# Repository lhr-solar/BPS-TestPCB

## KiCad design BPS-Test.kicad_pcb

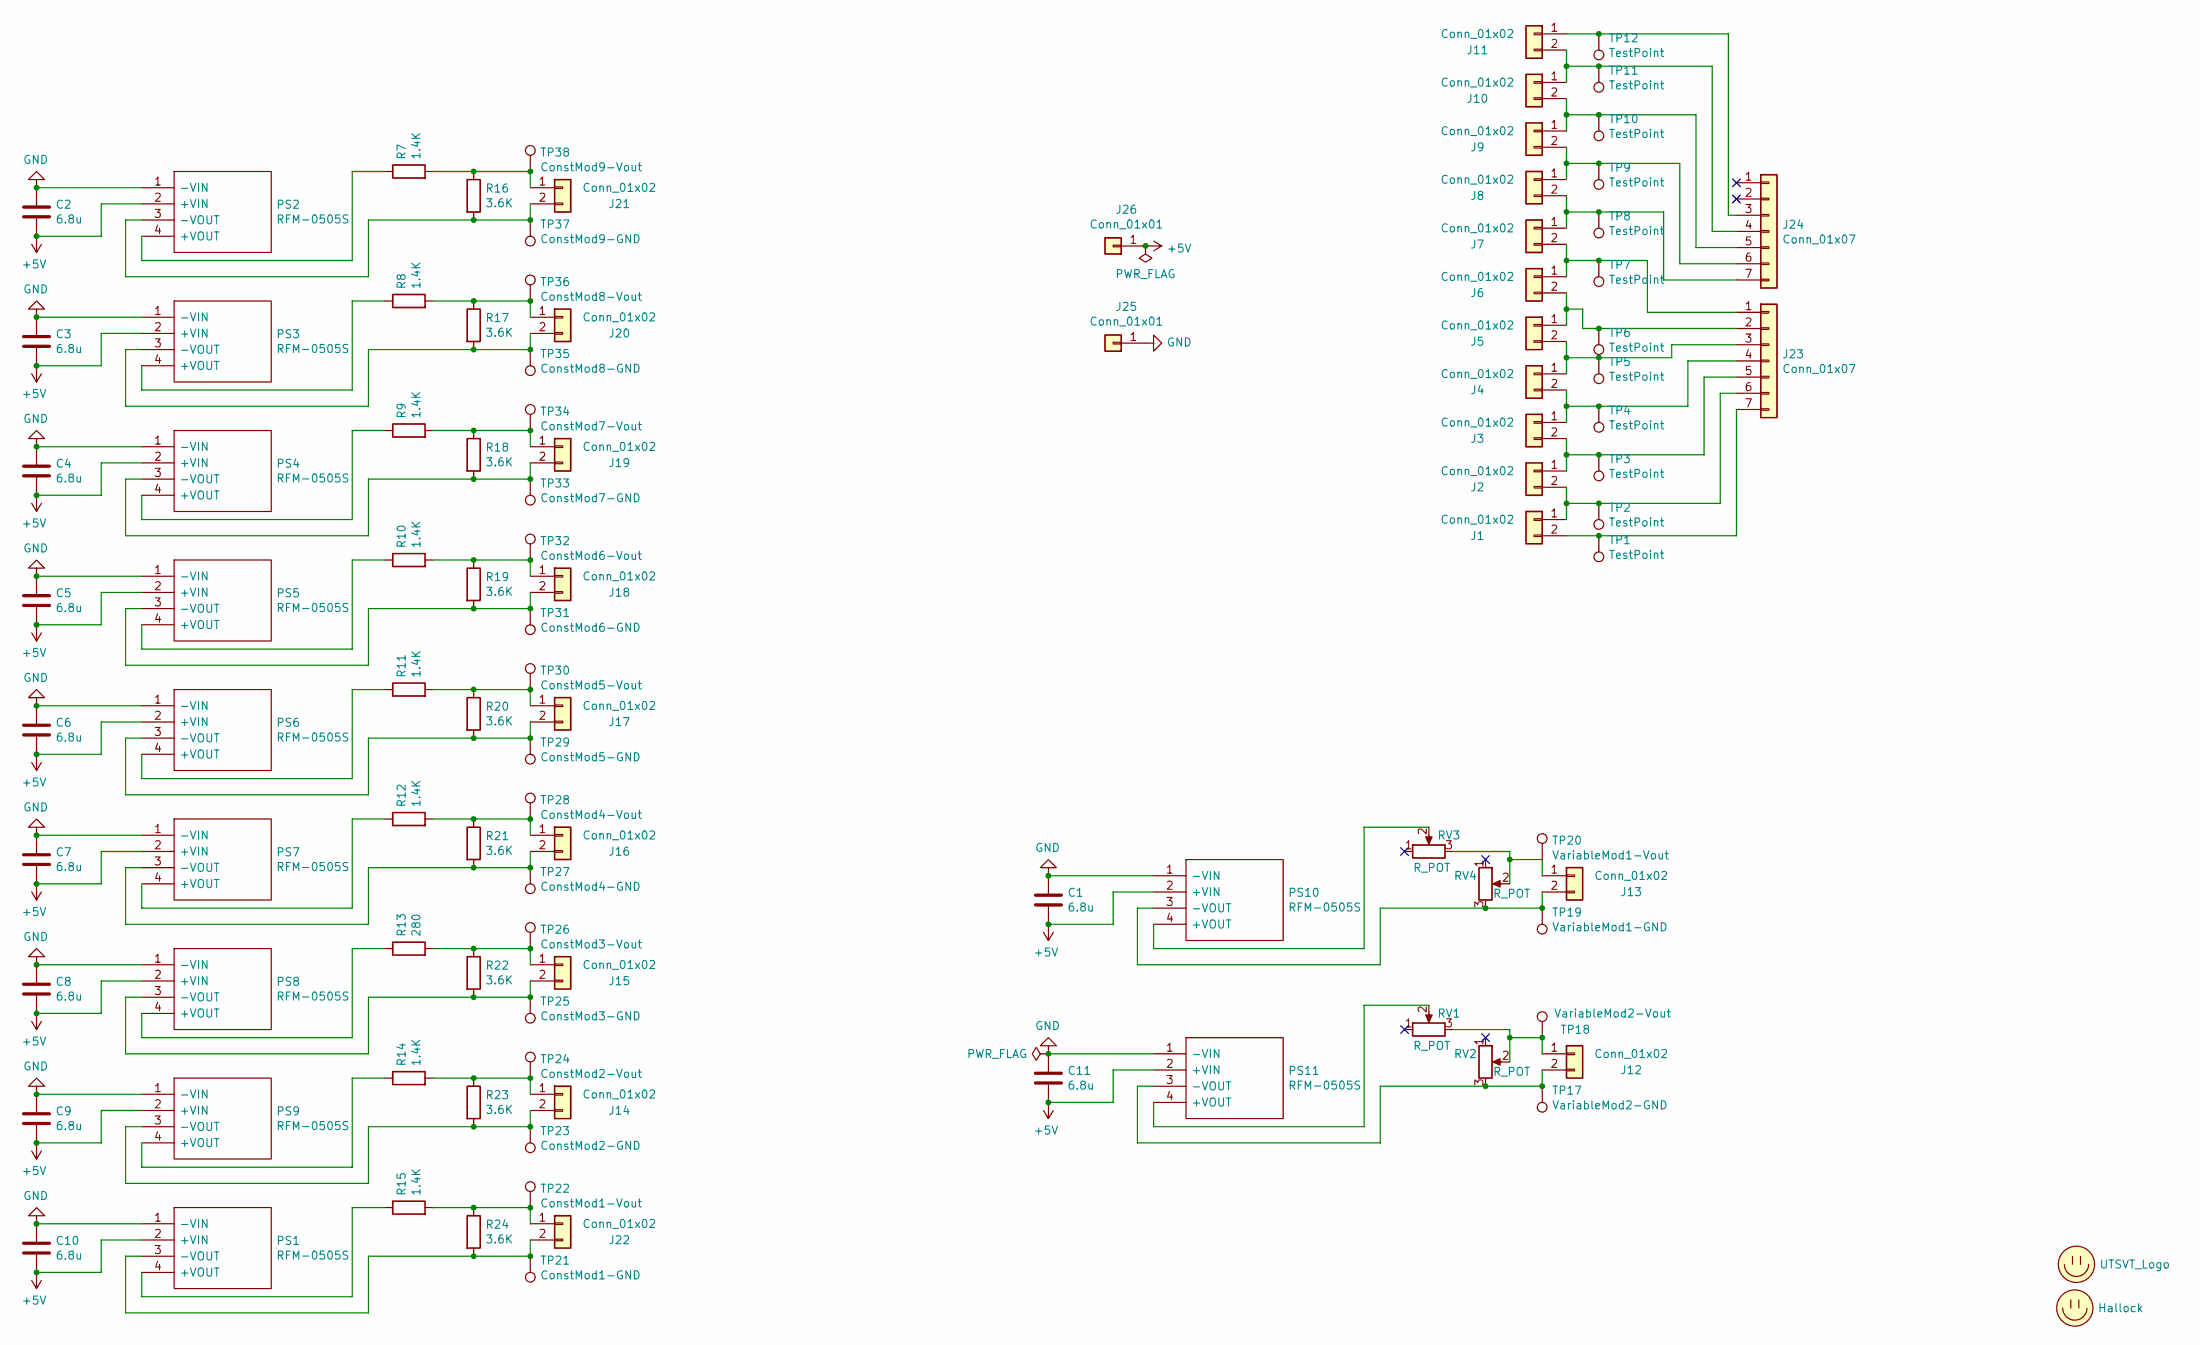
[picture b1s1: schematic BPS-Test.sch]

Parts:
C1, C2, C3, C4, C5, C6, C7, C8, C9, C10, C11: 6.8u; C_0805_2012Metric
J1, J2, J3, J4, J5, J6, J7, J8, J9, J10, J11, J12, J13, J14, J15, J16, J17, J18, J19, J20, J21, J22: Conn_01x02; PinHeader_1x02_P2.54mm_Vertical
J23, J24: Conn_01x07; Molex_MicroFit_01x07_Horizontal
J25, J26: Conn_01x01; Banana_Jack_1_Pin_4mm
LOGO1: Hallock; Hallock_Image
LOGO2: UTSVT_Logo; UTSVT_Logo_Symbol
PS1, PS2, PS3, PS4, PS5, PS6, PS7, PS8, PS9, PS10, PS11: RFM-0505S; RFM0505S; Mouser Part Number 919-RFM-0505S
R7, R8, R9, R10, R11, R12, R14, R15: 1.4K; R_0805_2012Metric
R13: 280; R_0805_2012Metric
R16, R17, R18, R19, R20, R21, R22, R23, R24: 3.6K; R_0805_2012Metric
RV1, RV2, RV3, RV4: R_POT; Potentiometer_Piher_PT-6-V_Vertical_Hole
TP1, TP2, TP3, TP4, TP5, TP6, TP7, TP8, TP9, TP10, TP11, TP12: TestPoint; TestPoint_Pad_2.0x2.0mm
TP17: VariableMod2-GND; TestPoint_Pad_2.0x2.0mm
TP18: VariableMod2-Vout; TestPoint_Pad_2.0x2.0mm
TP19: VariableMod1-GND; TestPoint_Pad_2.0x2.0mm
TP20: VariableMod1-Vout; TestPoint_Pad_2.0x2.0mm
TP21: ConstMod1-GND; TestPoint_Pad_2.0x2.0mm
TP22: ConstMod1-Vout; TestPoint_Pad_2.0x2.0mm
TP23: ConstMod2-GND; TestPoint_Pad_2.0x2.0mm
TP24: ConstMod2-Vout; TestPoint_Pad_2.0x2.0mm
TP25: ConstMod3-GND; TestPoint_Pad_2.0x2.0mm
TP26: ConstMod3-Vout; TestPoint_Pad_2.0x2.0mm
TP27: ConstMod4-GND; TestPoint_Pad_2.0x2.0mm
TP28: ConstMod4-Vout; TestPoint_Pad_2.0x2.0mm
TP29: ConstMod5-GND; TestPoint_Pad_2.0x2.0mm
TP30: ConstMod5-Vout; TestPoint_Pad_2.0x2.0mm
TP31: ConstMod6-GND; TestPoint_Pad_2.0x2.0mm
TP32: ConstMod6-Vout; TestPoint_Pad_2.0x2.0mm
TP33: ConstMod7-GND; TestPoint_Pad_2.0x2.0mm
TP34: ConstMod7-Vout; TestPoint_Pad_2.0x2.0mm
TP35: ConstMod8-GND; TestPoint_Pad_2.0x2.0mm
TP36: ConstMod8-Vout; TestPoint_Pad_2.0x2.0mm
TP37: ConstMod9-GND; TestPoint_Pad_2.0x2.0mm
TP38: ConstMod9-Vout; TestPoint_Pad_2.0x2.0mm

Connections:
+5V: C1.2, C2.2, C3.2, C4.2, C5.2, C6.2, C7.2, C8.2, C9.2, C10.2, C11.2, J26.1, PS1.2 (+VIN), PS2.2 (+VIN), PS3.2 (+VIN), PS4.2 (+VIN), PS5.2 (+VIN), PS6.2 (+VIN), PS7.2 (+VIN), PS8.2 (+VIN), PS9.2 (+VIN), PS10.2 (+VIN), PS11.2 (+VIN)
GND: C1.1, C2.1, C3.1, C4.1, C5.1, C6.1, C7.1, C8.1, C9.1, C10.1, C11.1, J25.1, PS1.1 (-VIN), PS2.1 (-VIN), PS3.1 (-VIN), PS4.1 (-VIN), PS5.1 (-VIN), PS6.1 (-VIN), PS7.1 (-VIN), PS8.1 (-VIN), PS9.1 (-VIN), PS10.1 (-VIN), PS11.1 (-VIN)
unnamed: J1.1, J2.2, J23.6, TP2.1
unnamed: J1.2, J23.7, TP1.1
unnamed: J2.1, J3.2, J23.5, TP3.1
unnamed: J10.1, J11.2, J24.4, TP11.1
unnamed: J9.1, J10.2, J24.5, TP10.1
unnamed: J11.1, J24.3, TP12.1
unnamed: J12.1, RV1.3, RV2.2, TP18.1
unnamed: J12.2, PS11.3 (-VOUT), RV2.3, TP17.1
unnamed: J13.1, RV3.3, RV4.2, TP20.1
unnamed: J13.2, PS10.3 (-VOUT), RV4.3, TP19.1
unnamed: J14.1, R14.2, R23.1, TP24.1
unnamed: J14.2, PS9.3 (-VOUT), R23.2, TP23.1
unnamed: J15.1, R13.2, R22.1, TP26.1
unnamed: J15.2, PS8.3 (-VOUT), R22.2, TP25.1
unnamed: J16.1, R12.2, R21.1, TP28.1
unnamed: J16.2, PS7.3 (-VOUT), R21.2, TP27.1
unnamed: J17.1, R11.2, R20.1, TP30.1
unnamed: J17.2, PS6.3 (-VOUT), R20.2, TP29.1
unnamed: J18.1, R10.2, R19.1, TP32.1
unnamed: J18.2, PS5.3 (-VOUT), R19.2, TP31.1
unnamed: J19.1, R9.2, R18.1, TP34.1
unnamed: J19.2, PS4.3 (-VOUT), R18.2, TP33.1
unnamed: J20.1, R8.2, R17.1, TP36.1
unnamed: J20.2, PS3.3 (-VOUT), R17.2, TP35.1
unnamed: J21.1, R7.2, R16.1, TP38.1
unnamed: J21.2, PS2.3 (-VOUT), R16.2, TP37.1
unnamed: J22.1, R15.2, R24.1, TP22.1
unnamed: J22.2, PS1.3 (-VOUT), R24.2, TP21.1
unnamed: J6.1, J7.2, J23.1, TP7.1
unnamed: J5.1, J6.2, J23.2, TP6.1
unnamed: J4.1, J5.2, J23.3, TP5.1
unnamed: J3.1, J4.2, J23.4, TP4.1
unnamed: J8.1, J9.2, J24.6, TP9.1
unnamed: J7.1, J8.2, J24.7, TP8.1
unnamed: PS1.4 (+VOUT), R15.1
unnamed: PS2.4 (+VOUT), R7.1
unnamed: PS3.4 (+VOUT), R8.1
unnamed: PS4.4 (+VOUT), R9.1
unnamed: PS5.4 (+VOUT), R10.1
unnamed: PS6.4 (+VOUT), R11.1
unnamed: PS7.4 (+VOUT), R12.1
unnamed: PS8.4 (+VOUT), R13.1
unnamed: PS9.4 (+VOUT), R14.1
unnamed: PS10.4 (+VOUT), RV3.2
unnamed: PS11.4 (+VOUT), RV1.2

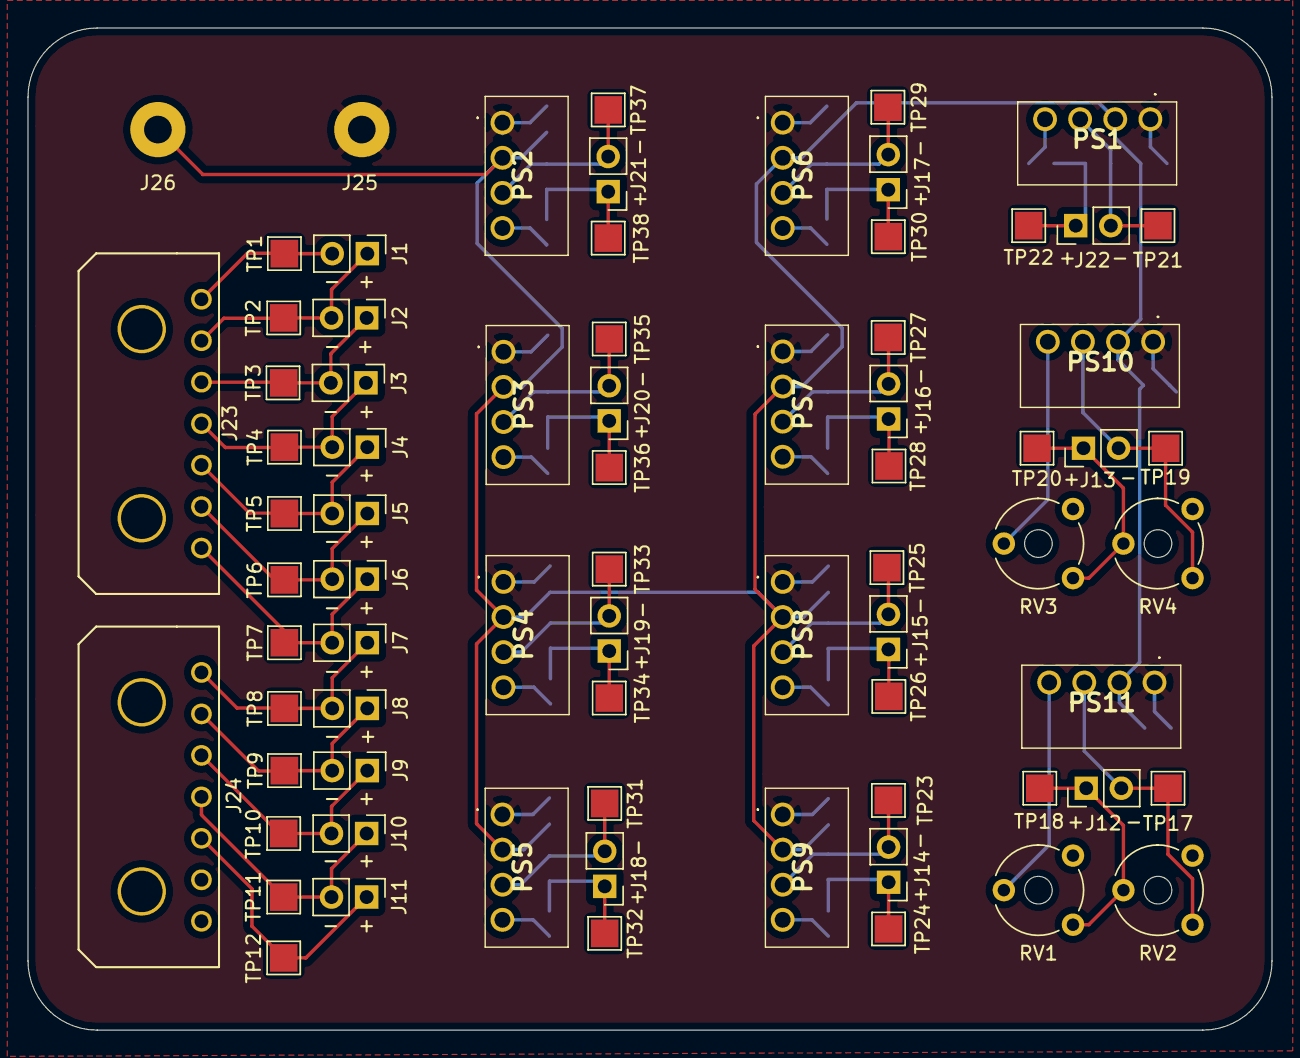
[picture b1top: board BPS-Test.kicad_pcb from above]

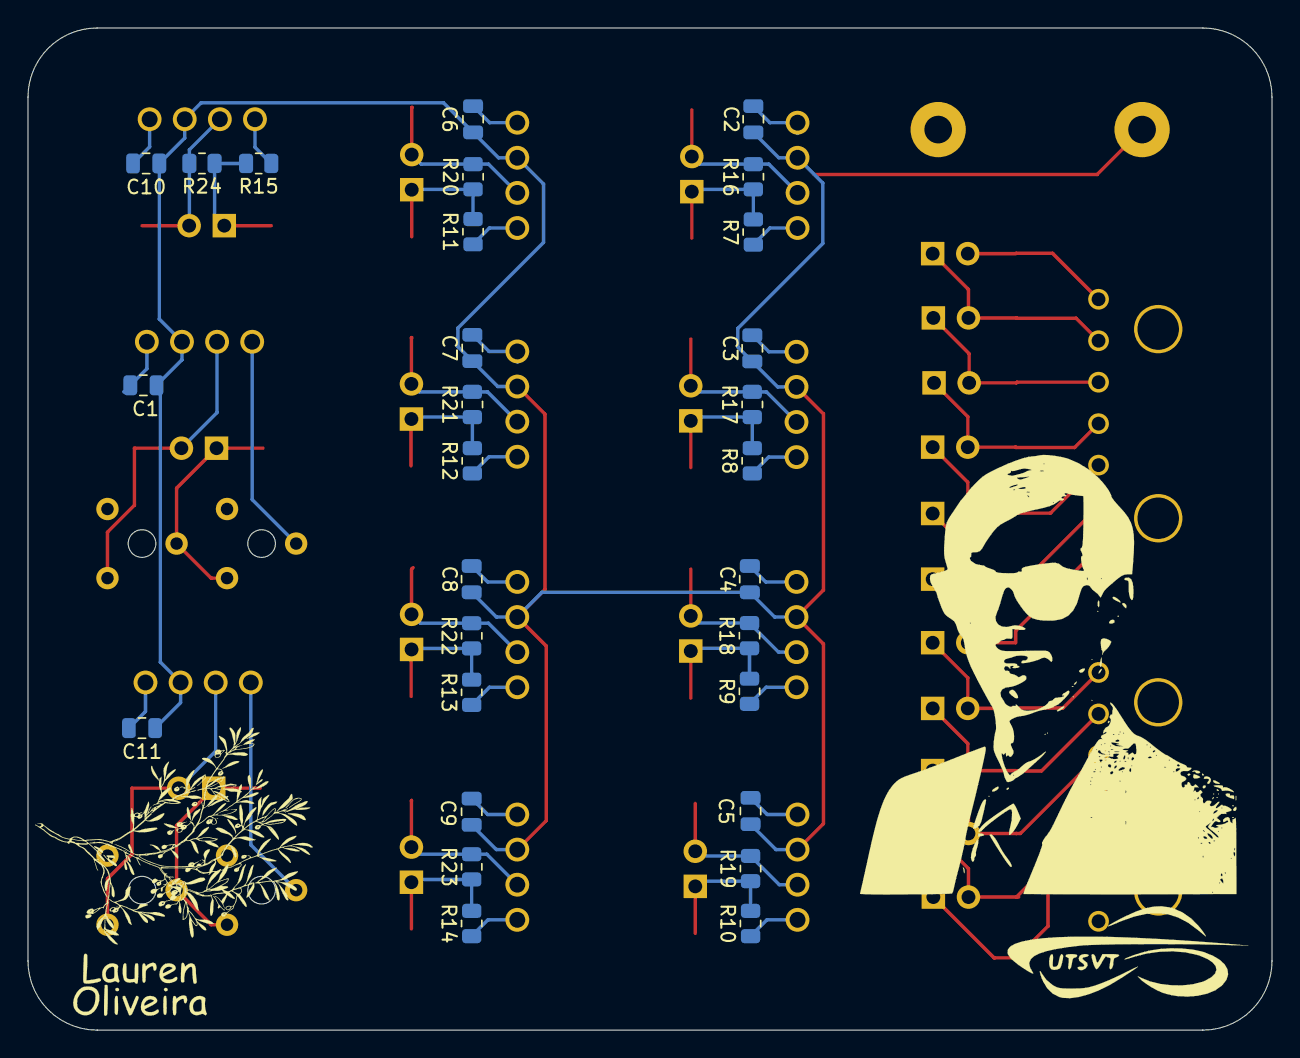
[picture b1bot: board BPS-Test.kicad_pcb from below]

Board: 2 copper layers, 90.0 x 72.5 mm, 106 parts (31 on the bottom side), 47 nets.

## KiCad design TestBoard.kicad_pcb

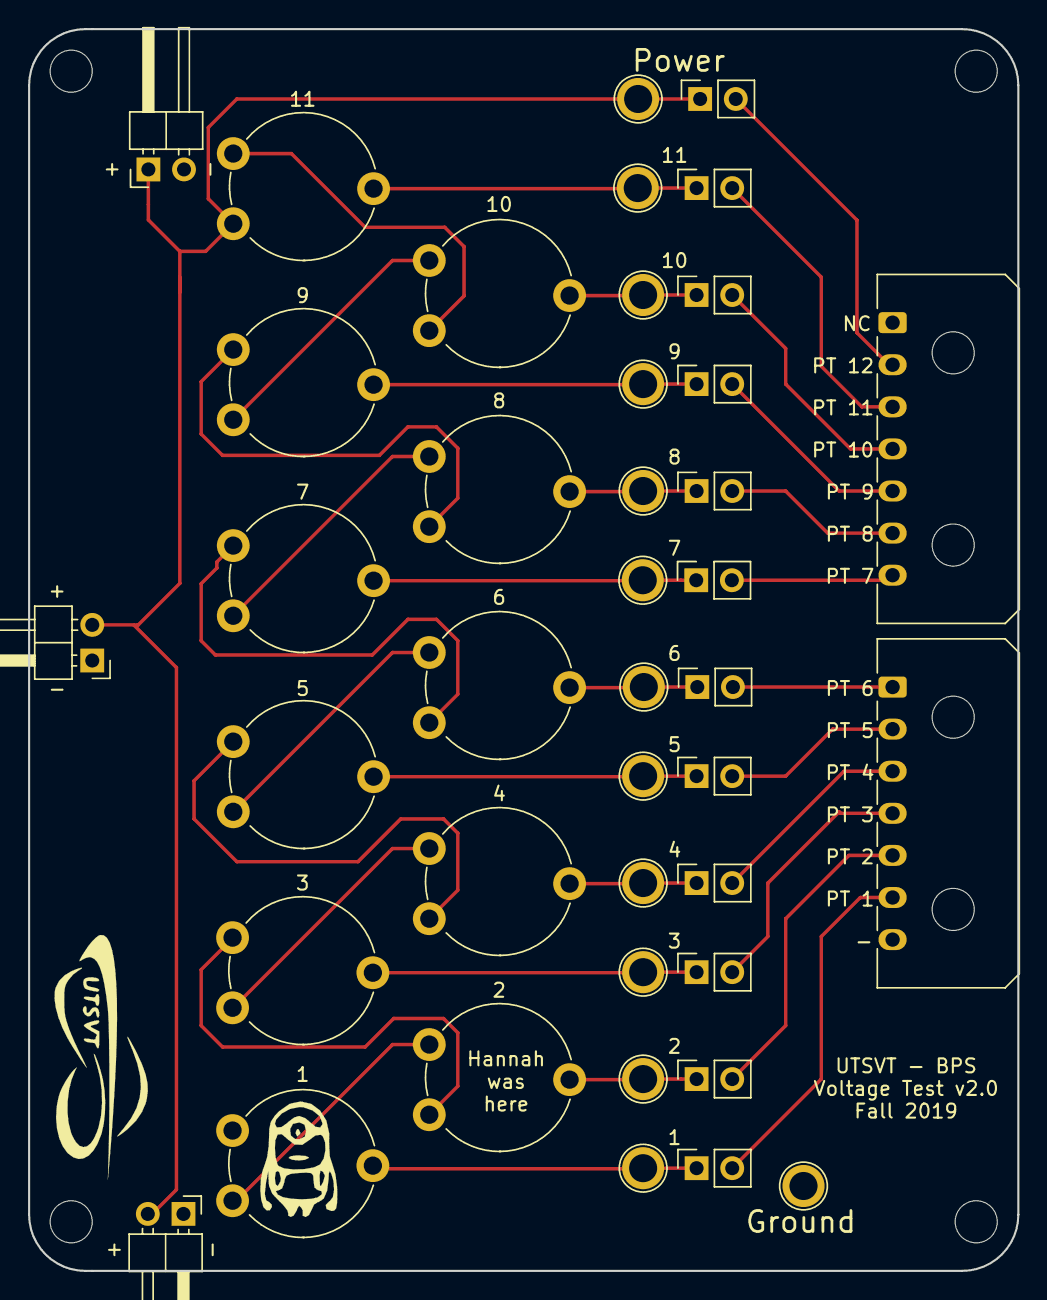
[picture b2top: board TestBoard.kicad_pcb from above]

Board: 2 copper layers, 70.5 x 88.5 mm, 45 parts (0 on the bottom side), 35 nets.

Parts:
H1, H2, H3, H4: MountingHole; MountingHole_3mm
J1, J4, J5: Conn_01x02; PinHeader_1x02_P2.54mm_Horizontal
J2, J3: Conn_01x07; Molex_Micro-Fit_3.0_43650-0700_1x07_P3.00mm_Horizontal
JP1, JP2, JP3, JP4, JP5, JP6, JP7, JP8, JP9, JP10, JP11, JP12: Jumper; PinSocket_1x02_P2.54mm_Vertical
RV1, RV2, RV3, RV4, RV5, RV6, RV7, RV8, RV9, RV10, RV11: R_POT; Potentiometer_Piher_PT-10-V10_Vertical
TP1, TP2, TP3, TP4, TP5, TP6, TP7, TP8, TP9, TP10, TP11, TP12, TP13: TestPoint; TestPoint_Plated_Hole_D2.0mm

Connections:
+36V: J1.2, J4.1, J5.2, JP12.1, RV1.1, TP12.1
GND: J1.1, J3.7, J4.2, J5.1, RV11.3, TP13.1
unnamed: J2.2, JP12.2
unnamed: J2.3, JP1.2
unnamed: J2.4, JP2.2
unnamed: J2.5, JP3.2
unnamed: J2.6, JP4.2
unnamed: J2.7, JP5.2
unnamed: J3.1, JP6.2
unnamed: J3.2, JP7.2
unnamed: J3.3, JP8.2
unnamed: J3.4, JP9.2
unnamed: J3.5, JP10.2
unnamed: J3.6, JP11.2
unnamed: JP1.1, RV1.2, TP1.1
unnamed: JP2.1, RV2.2, TP2.1
unnamed: JP3.1, RV3.2, TP3.1
unnamed: JP4.1, RV4.2, TP4.1
unnamed: JP5.1, RV5.2, TP5.1
unnamed: JP6.1, RV6.2, TP6.1
unnamed: JP7.1, RV7.2, TP7.1
unnamed: JP8.1, RV8.2, TP8.1
unnamed: JP9.1, RV9.2, TP9.1
unnamed: JP10.1, RV10.2, TP10.1
unnamed: JP11.1, RV11.2, TP11.1
unnamed: RV1.3, RV2.1
unnamed: RV2.3, RV3.1
unnamed: RV3.3, RV4.1
unnamed: RV4.3, RV5.1
unnamed: RV5.3, RV6.1
unnamed: RV6.3, RV7.1
unnamed: RV7.3, RV8.1
unnamed: RV8.3, RV9.1
unnamed: RV9.3, RV10.1
unnamed: RV10.3, RV11.1

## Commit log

2020-08-02 Set up for own repo
2020-10-03 Adds QuAC
2020-11-28 Add files via upload
    This is the new BPSTestBoard for this coming year. I uploaded a new file because when we started we did it local.
2020-12-12 Add files via upload
    New Test Board design for 2020.
2020-12-19 fixing Libraries and schematic changes
2020-12-19 more edits to schematic and began laying out pcb
2020-12-19 Finished just needs to be double checked
2020-12-20 Updates submodule
2021-01-06 Redoes layout to make the board smaller
2021-01-06 Cleans up repo by adding symbols and footprints to the common library
2021-01-06 Adds names
2021-01-11 Simplifies variable circuitry and adds gerbers
2021-01-11 Removes common to resolve merge conflict
2021-02-13 Added 3D models
2021-10-09 Updates branch for merge
2021-10-09 Updates with the new version
2021-10-09 Updates master with the most recent version
2021-10-09 Adds submodule
2021-10-16 Complete redesign of BPS Test board
